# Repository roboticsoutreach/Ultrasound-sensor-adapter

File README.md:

## Ultrasound mouning board for HC-SR04 ultrasound modules

This board is a mounting adapter for the ultrasound modules it contains a screw terminal and a power smoothing capacitor along with mounting holes to attach the board.

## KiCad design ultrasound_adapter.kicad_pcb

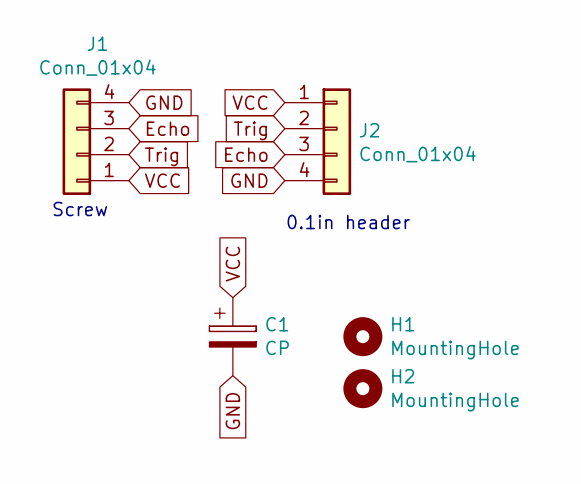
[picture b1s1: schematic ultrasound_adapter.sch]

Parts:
C1: CP; CP_Radial_D6.3mm_P2.50mm
H1, H2: MountingHole; MountingHole_3.2mm_M3_DIN965_Pad
J1: Conn_01x04; Socket_Strip_Straight_1x04_Pitch2.54mm
J2: Conn_01x04; Screw_terminals

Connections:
Echo: J1.3, J2.3
GND: C1.2, J1.4, J2.4
Trig: J1.2, J2.2
VCC: C1.1, J1.1, J2.1

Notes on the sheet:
0.1in header
Screw

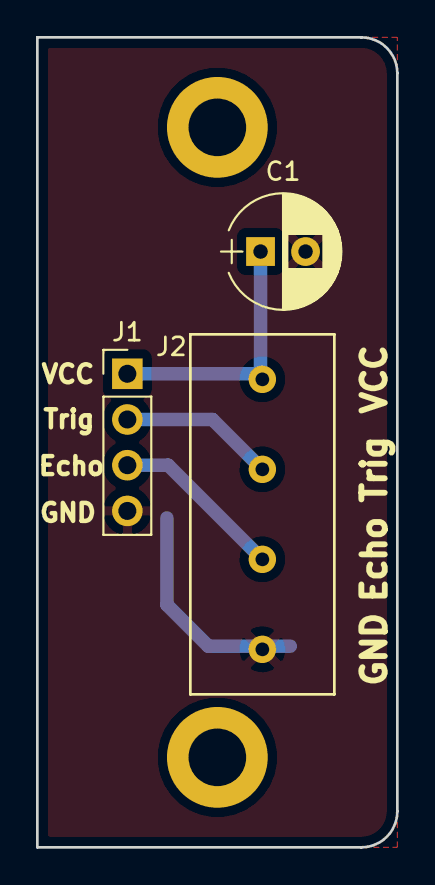
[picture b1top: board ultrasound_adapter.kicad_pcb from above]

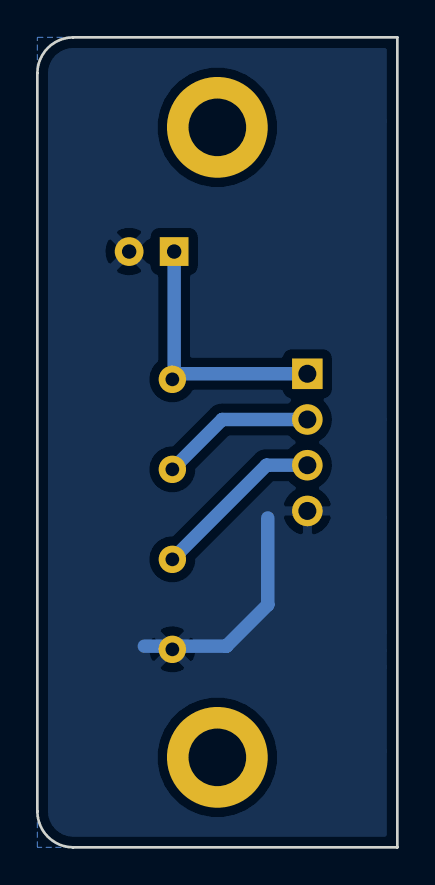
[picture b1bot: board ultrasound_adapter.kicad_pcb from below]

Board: 2 copper layers, 20.0 x 45.0 mm, 5 parts (2 on the bottom side), 4 nets.

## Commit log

2019-05-29 Files uploaded after first draft of PCB completed
2019-06-08 Added mounting holes and changed capacitor to be a large Electrolytic
2019-06-10 size increased, mounting holes made to be M3, layout changed
2019-07-13 Removed backup file
2019-07-13 Added gitignore
2019-07-13 Removed more gitignored files
2019-07-13 Updated board to add outline.
    Also added readme
2019-07-13 removed old gerber files
2019-07-13 Moved screw terminal back as it is larger than the silkscreen
2019-07-13 Added revision info to board
2019-07-14 Added labels to schematic frame
